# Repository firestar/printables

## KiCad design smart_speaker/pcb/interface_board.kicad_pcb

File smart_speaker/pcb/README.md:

# Round speaker interface board

A 4-layer, 54.5 x 62 mm carrier for the electronics bay. The ESP32 devkit plugs into two
sockets; the amp and both mics stay on their own boards and connect by cable. Pin
assignments match `../firmware/include/config.h`, so the firmware does not change.

**ESP32 footprint:** the row spacing (25.4 mm) and pin 1 position (9.6 mm from the USB-end
board edge) were scaled off the listing's photo, then confirmed by test-fitting a real devkit
in the printed plate from `esp32_fit_gauge.py`. The plate has loose 1.5 mm holes, so it
confirms the layout but not small errors.

**Parts and labels:** the board shows references only; values are in [`../PCB_PARTS.md`](../PCB_PARTS.md).

## Ports

Pin 1 has the square pad. Labels are on the silkscreen.

| Port | Ref | Connector | Pin 1 → 5 |
|---|---|---|---|
| MIC L | J3 | 5-pin JST SM pigtail, soldered | GND, 3V3, SCK, WS, SD |
| MIC R | J4 | 5-pin JST SM pigtail, soldered | GND, 3V3, SCK, WS, SD |
| AMP | J5 | 5-pin JST SM pigtail, soldered | GND, 5V, LRC, BCK, DIN |
| LED | J6 | 5-pin JST SM pigtail, soldered | GND, 5V, DIN, unused, unused |
| 5V IN | J7 | 2 wires from the barrel connector, up to 18 AWG | GND, +5V |

- **Speaker:** wires straight to the amp's screw terminal, with your 2-pin JST ZH inline if
  you want a plug. It is not on this board.
- **Mic L/R pin:** there is no wire for it. Jumper it at each mic: GND on the left mic, VDD
  on the right mic.
- **Amp:** GAIN and SD stay unconnected.
- **LED strip:** cut off its 3-pin plug. Thread the wires through the wall slot first, then
  fit the 5-pin connector, which won't fit through the 12 x 7 mm slot.

**The 5-pin connectors are interchangeable.** A mic plugged into AMP or LED gets 5 V on its
3.3 V pin and will probably die. Mark every cable before first power-up.

## Assembly

1. Solder Q1, U1, R1, R2 and C2-C6, then C1 (`+` is marked; the square pad is positive).
2. **Bridge JP1, or the LEDs get no data.** 2-3 uses the level shifter (fit by default);
   1-2 bypasses it.
3. Solder the two 15-pin sockets on top, keeping them square.
4. For each cable, pass the wires through the slot, over the bar, into the holes from the
   top, and solder underneath. The slot takes the pull, not the joints.
5. Before plugging in the ESP32, power up from the 5 V input and check: 5 V at J5 pin 2,
   J6 pin 2 and J1 pin 1; no short on J2 pin 1 (3V3).
6. Fit the board with 4 x M2.5 x 6 self-tapping screws into the new base bosses.
7. Plug in the ESP32 with the USB connector at the `USB END >>` side, module up. **Turned
   180° it still fits, and that would misconnect power.**

## Fit

The sockets are 8.5 mm tall, so the board top sits at z 9 with the ESP32 on its existing
20 mm ledges. `../round_sub/base.stl` now has 4 screw bosses for it, so **the base needs
reprinting**. `check_fit.py` in `../round_sub/` passes with the board, sockets and C1 modeled.

## Layers

| Layer | Use |
|---|---|
| F.Cu | Signals, parts, GND fill |
| In1.Cu | Solid GND |
| In2.Cu | 5 V plane |
| B.Cu | Signals, GND fill |

3V3 is a routed trace rather than the small plane island first planned, because the mics
draw so little. Fab settings: 1.6 mm, 1 oz outer, minimum 0.2 mm track/gap, 0.3 mm via
drill. Give the fab `interface_board-gerbers.zip`.

## Files

| File | What |
|---|---|
| `make_pcb.py` | Parts, nets, placement and the router; generates the board |
| `export.sh` | Rebuilds everything using KiCad 9 in Docker |
| `check_board.py` | Checks the saved board and Gerbers against the pin map |
| `check_gerbers.py` | Rebuilds connections from the Gerbers with an independent parser |
| `trace_circuits.py` | Lists every circuit traced from the Gerber copper |
| `interface_board.kicad_pcb` / `.kicad_pro` | KiCad project; opens in KiCad 9 |
| `netlist.csv` | Every connection, in place of a schematic |
| `BOM.csv` | Parts list |
| `drc.rpt` | KiCad's design-rule report |
| `render/` | Top and bottom pictures, plus each copper layer |

There is no KiCad schematic file: the board is generated straight from the net tables in
`make_pcb.py`. KiCad's board-versus-schematic check therefore doesn't apply, and
`check_board.py` does that job instead. Editing the board by hand in KiCad means the next
`make_pcb.py` run overwrites the edits.

## Requirements from the 2-layer simulations

The same circuit was simulated in `../pcb_2layer/sim/`, and the planes here have less resistance than
the 2-layer copper. Those results apply: supply at least 4.9 V under load, C1 general purpose with
ESR 0.1 ohm or more, JP1 on 2-3, and R3/R4 fitted. The 4-layer copper itself was not simulated.

## Not proven yet

- No board has been built, so none of this has been tested electrically.
- Q1 passes the 3.4 A peak but has only modest copper for cooling; it dissipates about
  0.6 W at that peak, and far less at the typical 0.4 A. Check its temperature at full LED
  brightness.
- Mic SCK, WS and SD run side by side for about 40 mm over the ground plane. This should be
  fine at about 1 MHz, but listen for noise on the mics.
- BOM prices are rough estimates, not live quotes.

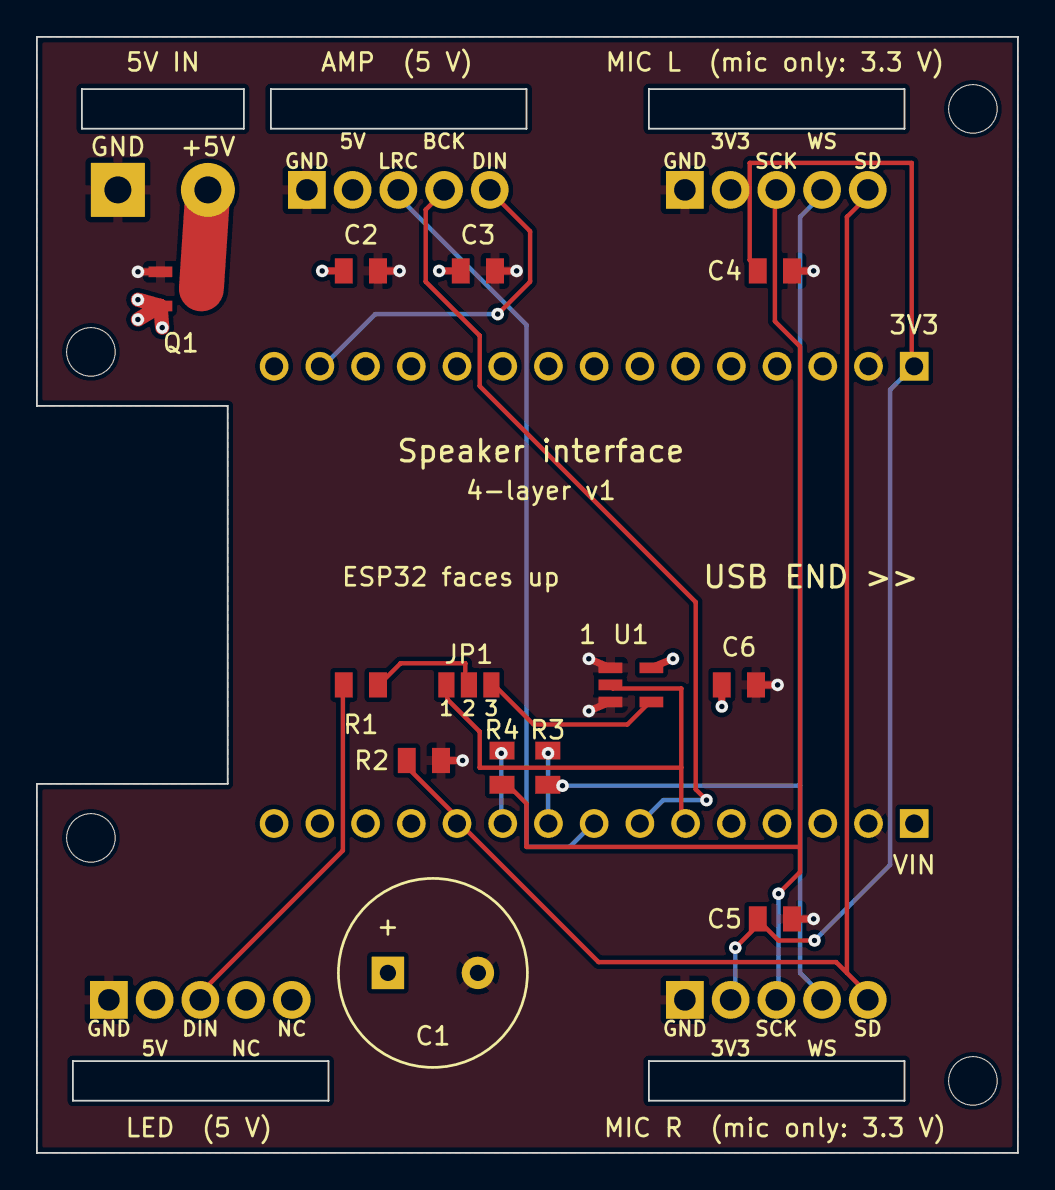
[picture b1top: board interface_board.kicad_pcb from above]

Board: 4 copper layers, 54.5 x 62.0 mm, 24 parts (0 on the bottom side), 16 nets.

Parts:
C1: 1000uF 10V, 10x12.5mm; C1
C2: 10uF 10V 0805; C2
C3: 100nF 0805; C3
C4: 100nF 0805; C4
C5: 100nF 0805; C5
C6: 100nF 0805; C6
H1, H2, H3, H4: M2.5; MOUNT
J1: Socket 1x15 2.54mm, ESP32 VIN row; J1
J2: Socket 1x15 2.54mm, ESP32 3V3 row; J2
J3: MIC L: 5-pin JST SM pigtail; J3
J4: MIC R: 5-pin JST SM pigtail; J4
J5: AMP: 5-pin JST SM pigtail; J5
J6: LED: 5-pin JST SM pigtail; J6
J7: 5V IN: 2 wires, up to 18 AWG; J7
JP1: LED data: 1-2 bypass, 2-3 shifter; JP1
Q1: AO3401A; Q1
R1: 330R 0805; R1
R2: 100k 0805; R2
R3: 100R 0805; R3
R4: 100R 0805; R4
U1: 74AHCT1G125; U1

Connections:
+3V3: C4.1, C5.1, J2.1, J3.2, J4.2
+5V: C1.1, C2.1, C3.1, C6.1, J1.1, J5.2, J6.2, Q1.2, U1.5
GND: C1.2, C2.2, C3.2, C4.2, C5.2, C6.2, J1.2, J2.2, J3.1, J4.1, J5.1, J6.1, J7.1, Q1.1, R2.2, U1.1, U1.3
LED_BUF: JP1.3, U1.4
LED_OUT: J6.3, R1.1
LED_RAW: J1.6, JP1.1, U1.2
LED_SEL: JP1.2, R1.2
MIC_SCK: J3.3, J4.3, R4.2
MIC_SD: J1.11, J3.5, J4.5, R2.1
MIC_WS: J3.4, J4.4, R3.2
SCK_ESP: J1.10, R4.1
SPK_BCLK: J1.7, J5.4
SPK_DIN: J2.14, J5.5
SPK_LRC: J1.8, J5.3
VIN_RAW: J7.2, Q1.3
WS_ESP: J1.9, R3.1

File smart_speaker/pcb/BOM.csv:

ref,qty,part,notes,est_usd_each
PCB,1,4-layer PCB 54.5x62 mm 1.6 mm,from interface_board-gerbers.zip; fabs usually have a 5-board minimum; about $10-30 for 5 before shipping,4.00
J1 J2,2,Female socket 1x15 2.54 mm 8.5 mm tall,straight through-hole; height sets the board fit,0.40
J3 J4 J5 J6,4,JST SM 5-pin pigtail 22 AWG,you have these; board side soldered,0.00
J7,1,Screw-terminal barrel connector with 2 wires,you have this; board side soldered,0.00
Q1,1,AO3401A P-channel MOSFET SOT-23,reverse-polarity protection,0.10
U1,1,SN74AHCT1G125DBVR SOT-23-5,LED data level shifter; optional if JP1 is set to bypass,0.30
C1,1,1000 uF 10 V general-purpose electrolytic 10 x 12.5 mm 5 mm lead spacing,keep it 13.5 mm tall or less; ESR 0.1 ohm or more (not an ultra-low-ESR type) to limit plug-in current,0.30
C2,1,10 uF 10 V X5R 0805,amp port,0.05
C3 C4 C5 C6,4,100 nF 0805,decoupling,0.02
R1,1,330 ohm 0805,LED data,0.02
R2,1,100 kohm 0805,mic SD pull-down,0.02
R3 R4,2,100 ohm 0805,damp mic WS and SCK at the ESP32,0.02
Screws,4,M2.5 x 6 self-tapping,into base bosses,0.05

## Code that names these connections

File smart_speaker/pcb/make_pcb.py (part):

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           "35": "MIC_SD", "25": "SPK_LRC", "26": "SPK_BCLK", "22": "SPK_DIN",
           "27": "LED_RAW"}

MIC_PINS = [("GND", "GND"), ("3V3", "+3V3"), ("SCK", "MIC_SCK"), ("WS", "MIC_WS"),
            ("SD", "MIC_SD")]
AMP_PINS = [("GND", "GND"), ("5V", "+5V"), ("LRC", "SPK_LRC"), ("BCK", "SPK_BCLK"),
            ("DIN", "SPK_DIN")]
LED_PINS = [("GND", "GND"), ("5V", "+5V"), ("DIN", "LED_OUT"), ("NC", ""), ("NC", "")]


def K(x, y):
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def check_firmware_pins():
    cfg = os.path.join(HERE, "..", "firmware", "include", "config.h")
    text = open(cfg).read()
    want = {"PIN_SPK_BCLK": "SPK_BCLK", "PIN_SPK_LRC": "SPK_LRC", "PIN_SPK_DIN": "SPK_DIN",
            "PIN_MIC_SCK": "SCK_ESP", "PIN_MIC_WS": "WS_ESP", "PIN_MIC_SD": "MIC_SD",
            "PIN_LED": "LED_RAW"}
    for define, net in want.items():
        pin = re.search(rf"#define {define} (\d+)", text).group(1)
        assert ESP_NET.get(pin) == net, f"{define}={pin} but board has {ESP_NET.get(pin)}"
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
